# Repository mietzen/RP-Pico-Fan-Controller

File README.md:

# WIP: Raspberry Pi Pico Fan Controller

This project aims to create a fan controller based on an RP2040 / RP2350 that can be hand-soldered by anyone and will run on any machine!
It uses only the bare minimum of through-hole solder parts to give you:

* 3 thermal sensors
* 6 controllable 12V PWM fans

The idea came up when I was building my home server with consumer parts and realized again that most onboard fan controllers don't work properly on Linux.

The project consists of three parts:

* The TinyGo RP Pico firmware, found in [firmware](https://github.com/mietzen/RP-Pico-Fan-Controller/tree/main/firmware)
* The Golang fan controller, found in [fancontroller](https://github.com/mietzen/RP-Pico-Fan-Controller/tree/main/fancontroller)
* The KiCad PCB design, found in [kicad](https://github.com/mietzen/RP-Pico-Fan-Controller/tree/main/kicad)

## Firmware

The firmware is waiting for commands over the serial usb interface, documented the `json` commands and responses [json-schema](https://github.com/mietzen/RP-Pico-Fan-Controller/tree/main/firmware/json-schema).

## Hardware Prototype

Here are some pictures from my prototype PCB that I’m using for development:

## TODOs

The project is still in development, I still have a couple of TODOs.

* [Incomplete documentation](https://github.com/mietzen/RP-Pico-Fan-Controller/issues/1)
* [Integrate lm-sensors readings](https://github.com/mietzen/RP-Pico-Fan-Controller/issues/2)
* [Emulate as hwmon device on Linux](https://github.com/mietzen/RP-Pico-Fan-Controller/issues/3)
* [Auto-detect which fans / sensors are connected](https://github.com/mietzen/RP-Pico-Fan-Controller/issues/4)
* [Show fans / sensors as disconnected in fan-controller](https://github.com/mietzen/RP-Pico-Fan-Controller/issues/5)
* [New PCB revision with rear-facing USB port](https://github.com/mietzen/RP-Pico-Fan-Controller/issues/6)
* [Create BOM](https://github.com/mietzen/RP-Pico-Fan-Controller/issues/7)

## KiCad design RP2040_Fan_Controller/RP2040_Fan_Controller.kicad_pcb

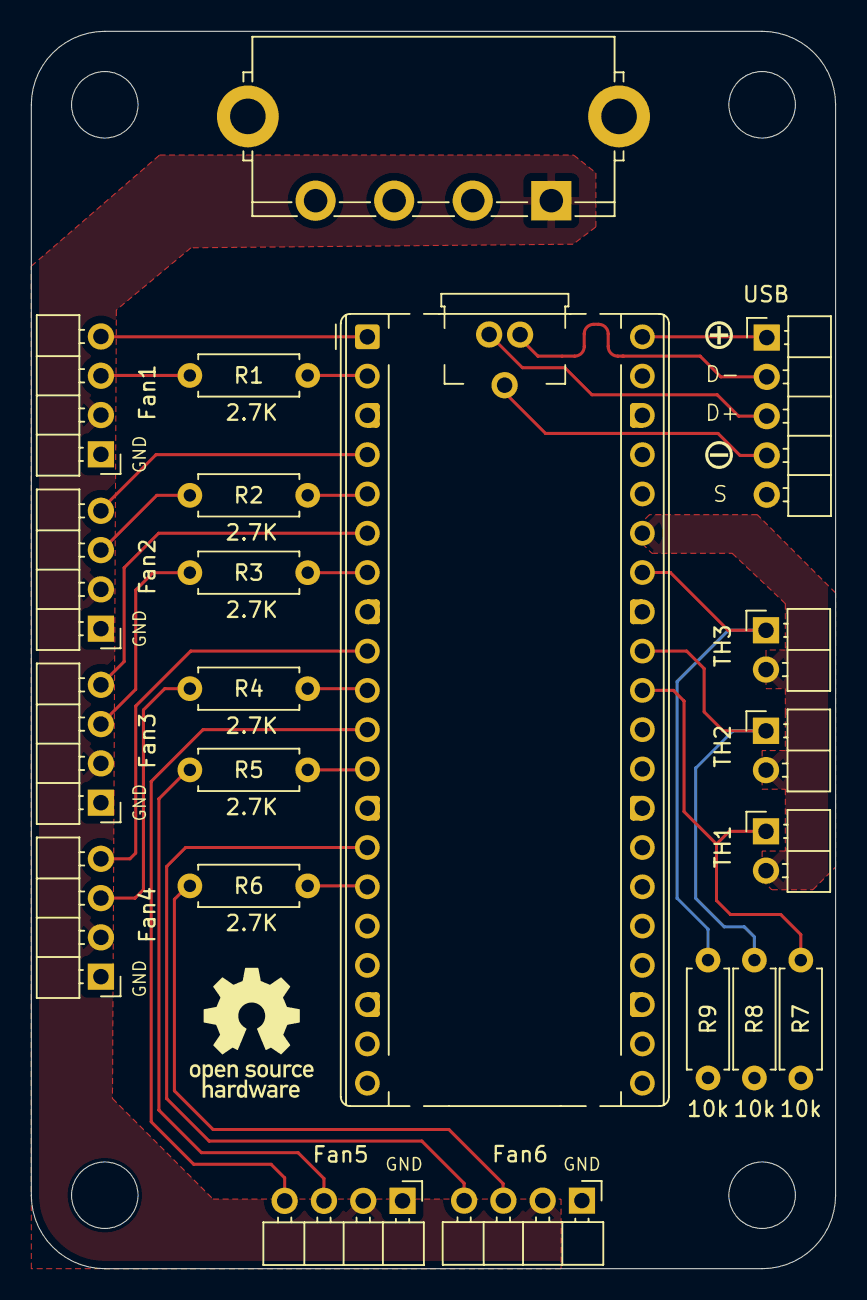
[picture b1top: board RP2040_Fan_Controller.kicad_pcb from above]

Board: 2 copper layers, 52.0 x 80.0 mm, 20 parts (0 on the bottom side), 26 nets.

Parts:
A1: RaspberryPi_Pico; RaspberryPi_Pico_Common_THT
Fan1, Fan2, Fan3, Fan4, Fan5, Fan6: Fan_4pin; PinHeader_1x04_P2.54mm_Horizontal
J1: USB; PinHeader_1x05_P2.54mm_Horizontal
R1, R2, R3, R4, R5, R6: 2.7K; R_Axial_DIN0207_L6.3mm_D2.5mm_P7.62mm_Horizontal
R7, R8, R9: 10k; R_Axial_DIN0207_L6.3mm_D2.5mm_P7.62mm_Horizontal
TH1, TH2, TH3: 10k; PinHeader_1x02_P2.54mm_Horizontal

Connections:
+12V: Fan1.2 (+), Fan2.2 (+), Fan3.2 (+), Fan4.2 (+), Fan5.2 (+), Fan6.2 (+)
ADC_0: A1.31 (GPIO26_ADC0), R7.2, TH1.1
ADC_1: A1.32 (GPIO27_ADC1), R8.2, TH2.1
ADC_2: A1.34 (GPIO28_ADC2), R9.2, TH3.1
ADC_GND: A1.33 (AGND), R7.1, R8.1, R9.1
ADC_VREF: A1.35 (ADC_VREF), TH1.2, TH2.2, TH3.2
GND: A1.3 (GND), A1.8 (GND), A1.13 (GND), A1.18 (GND), A1.23 (GND), A1.28 (GND), A1.38 (GND), Fan1.1 (-), Fan2.1 (-), Fan3.1 (-), Fan4.1 (-), Fan5.1 (-), Fan6.1 (-), J1.5 (Shield)
unnamed: Fan1.3 (Tacho), R1.1
unnamed: Fan2.3 (Tacho), R2.1
unnamed: Fan3.3 (Tacho), R3.1
unnamed: Fan4.3 (Tacho), R4.1
unnamed: Fan5.3 (Tacho), R5.1
unnamed: Fan6.3 (Tacho), R6.1
PWM_FAN1: A1.1 (GPIO0), Fan1.4 (PWM)
PWM_FAN2: A1.4 (GPIO2), Fan2.4 (PWM)
PWM_FAN3: A1.6 (GPIO4), Fan3.4 (PWM)
PWM_FAN4: A1.9 (GPIO6), Fan4.4 (PWM)
PWM_FAN5: A1.11 (GPIO8), Fan5.4 (PWM)
PWM_FAN6: A1.14 (GPIO10), Fan6.4 (PWM)
RPM_FAN1: A1.2 (GPIO1), R1.2
RPM_FAN2: A1.5 (GPIO3), R2.2
RPM_FAN3: A1.7 (GPIO5), R3.2
RPM_FAN4: A1.10 (GPIO7), R4.2
RPM_FAN5: A1.12 (GPIO9), R5.2
RPM_FAN6: A1.15 (GPIO11), R6.2
VBUS: A1.40 (VBUS), J1.1 (VBUS)

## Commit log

2025-06-08 Initial-Commit
2025-06-28 PCB-Rev 0.1.0
2025-06-28 PCB-Rev 0.2.0
2025-06-28 PCB-Rev 0.2.1
2025-06-28 PCB-Rev 0.3.0
2025-06-28 PCB-Rev 0.4.0
2025-06-28 updated gitignore
2025-06-28 PCB-Rev 1.0.0
2025-06-28 added svgs
2025-06-28 Better folder structure
2025-06-28 added tinygo fw
2025-06-28 Updated FW
2025-06-29 Added json schema
2025-06-29 Added host controller
2025-06-29 Use fork of deprecated yaml pkg
2025-06-29 Added SMNP support
2025-07-02 Refactored Firmware and added watchdog
2025-07-02 Minor Fixes & Refactoring
2025-07-02 Fix daemon and validate config
2025-07-02 fixed serial auto detection
2025-07-03 Refactoring: always give back status
2025-07-03 update gitignore
2025-07-03 cleanup kicad folder
2025-07-03 Rename host controller
2025-07-03 rename socket
2025-07-03 Set invalid temp and round to one decimal
2025-07-03 Fix json output
2025-07-03 Use atomic for interrupts
2025-07-03 Refactoring
2025-07-03 Added computeTemperature
2025-07-04 Introduce more cli setter & config editing via socket
2025-07-04 update help
2025-07-04 fix config writing
2025-07-04 remove old commands
2025-07-04 Updated CLI show
2025-07-05 Renamed module to fancontroller
2025-07-20 Added LICENSE
2025-11-06 Add project description and prototype images
2025-11-06 Add firmware documentation to README

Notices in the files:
RP2040_Fan_Controller/RP2040_Fan_Controller.kicad_pcb:
MIT License
